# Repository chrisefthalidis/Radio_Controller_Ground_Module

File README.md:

This board is an embedded system, based on the STM32F411CCU6 microcontroller. It incorporates an nRF24L01+ radio
transceiver with an analog front-end (RFX2401C) for signal amplification. Inside the 'Hardware' folder, you will
find all the necessary PCB design files from KiCad. Inside the 'Firmware' folder, you will find all the relevant
HAL drivers generated by STM32CubeMX, as well as an nRF24L01+ SPI driver. This board is complementary to the Flight
Controller board that you will find on my GitHub page. The basic idea is that we read the value of the on-board 
potentiometer through an ADC via DMA and we transmit this value via radio to the Flight Controller, which in turn
controls the speed of the quadcopter's motors.

P.S. This board is not perfect in any way. It has some design mistakes, because it's one of my earlier boards, but
it WORKS fine. With each board that i design, i learn new stuff and keep getting better. If you have any questions
on how to use this board, please contact me at chrisefthalidis@gmail.com

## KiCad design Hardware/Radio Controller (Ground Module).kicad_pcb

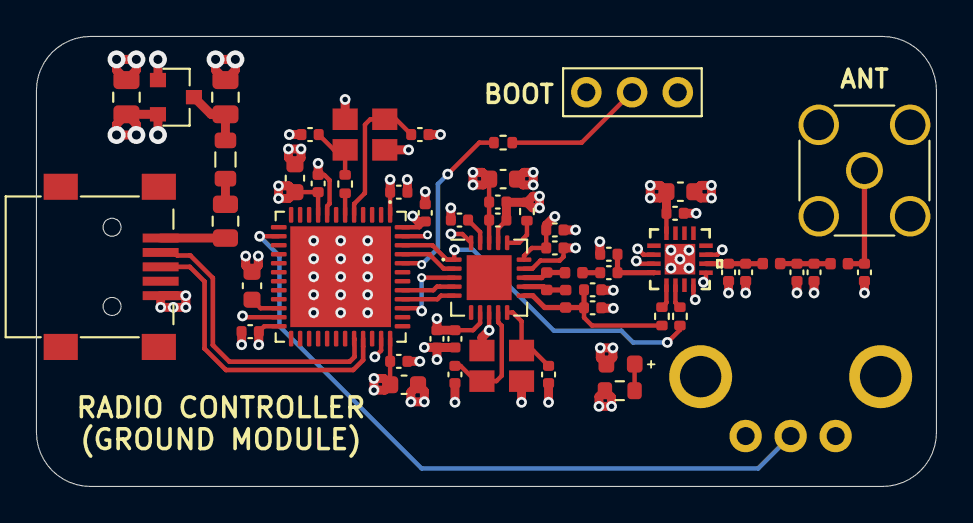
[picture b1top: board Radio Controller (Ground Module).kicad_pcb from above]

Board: 4 copper layers, 50.0 x 25.0 mm, 57 parts (0 on the bottom side), 34 nets.

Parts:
C1, C2: 10uF; C_0805_2012Metric
C3, C24, C31: 4.7uF; C_0603_1608Metric
C4, C6, C8: 10nF; C_0402_1005Metric
C5, C7, C9: 1nF; C_0402_1005Metric
C10, C29: 1uF; C_0603_1608Metric
C11: 220pF; C_0402_1005Metric
C12: 4.7pF; C_0402_1005Metric
C13: 2.2nF; C_0402_1005Metric
C14, C20, C21, C22, C23: 1.5pF; C_0402_1005Metric
C15: 1pF; C_0402_1005Metric
C16: 33nF; C_0402_1005Metric
C17, C18, C32, C33: 12pF; C_0402_1005Metric
C19: 0.3pF; C_0402_1005Metric
C25, C26, C27, C28, C30: 100nF; C_0402_1005Metric
D1: Green LED; LED_0603_1608Metric
F1: Fuse; Fuse_0805_2012Metric
FB1: GZ2012D601TF; L_0805_2012Metric
J1: USB_B_Mini; USB_Mini-B_Lumberg_2486_01_Horizontal
J2: KH-SMA-KE8-G; SMA_Amphenol_132291_Vertical
J3: Conn_01x03; PinHeader_1x03_P2.54mm_Vertical
L1: 2.7nH; L_0402_1005Metric
L2: 8.2nH; L_0402_1005Metric
L3: 3.9nH; L_0402_1005Metric
L4, L5: 2.4nH; L_0402_1005Metric
R1: 330Ω; R_0603_1608Metric
R2, R3: 1ΚΩ; R_0402_1005Metric
R4: 22ΚΩ; R_0402_1005Metric
R5: 10ΚΩ; R_0402_1005Metric
R6: 47Ω; R_0402_1005Metric
RV1: R_POT; Potentiometer_Alps_RK09K_Single_Horizontal
U1: XC6206P332MR; SOT-23
U2: RFX2401C
U3: nRF24L01P; QFN-20-1EP_4x4mm_P0.5mm_EP2.5x2.5mm
U4: STM32F411CCUx; QFN-48-1EP_7x7mm_P0.5mm_EP5.6x5.6mm
Y1, Y2: X322516MLB4SI; Crystal_SMD_3225-4Pin_3.2x2.5mm

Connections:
+3V3: C2.1, C3.1, C4.1, C5.1, C6.1, C7.1, C8.1, C9.1, C10.1, C11.1, C24.1, C25.1, C26.1, C27.1, C28.1, C29.1, C30.1, J3.1, R1.1, RV1.1, U1.2, U2.16, U3.7, U3.15, U3.18, U4.1, U4.9, U4.24, U4.36, U4.48
/ADC_IN: RV1.2, U4.14
/ANT: C19.1, C20.1, L4.2, U2.10
/ANT1: L1.2, L2.1, U3.12
/ANT2: L2.2, L3.2, U3.13
/BOOT0: R5.1, U4.44
/CE: R3.1, U3.1, U4.46
/CSN: U3.2, U4.45
/LDO_VIN: C1.1, FB1.1, U1.3
/LED_RES: D1.2, R1.2
/MISO: U3.5, U4.40
/MOSI: U3.4, U4.41
/OSC_IN: C32.1, U4.5, Y2.1
/OSC_OUT: R6.2, U4.6
/RXEN: R3.2, U2.6
/SCK: U3.3, U4.39
/TXEN: R2.2, U2.5
/TXRX: C14.1, C15.1, U2.4
/USB_D+: J1.3, U4.33
/USB_D-: J1.2, U4.32
/VCAP1: C31.2, U4.22
/VDD_PA: C12.1, C13.1, L1.1, R2.1, U3.11
/XC1: C17.1, U3.10, Y1.1
/XC2: C18.1, U3.9, Y1.3
GND: C1.2, C2.2, C3.2, C4.2, C5.2, C6.2, C7.2, C8.2, C9.2, C10.2, C11.2, C12.2, C13.2, C15.2, C16.2, C17.2, C18.2, C19.2, C20.2, C21.2, C22.2, C23.2, C24.2, C25.2, C26.2, C27.2, C28.2, C29.2, C30.2, C31.1, C32.2, C33.2, D1.1, J1.5, J2.2, J3.3, R4.1, RV1.3, U1.1, U2.2, U2.3, U2.8, U2.9, U2.11, U2.17, U3.8, U3.14, U3.17, U3.20, U4.8, U4.23, U4.35, U4.47, U4.49, Y1.2, Y1.4, Y2.2, Y2.4
unnamed: C14.2, L3.1
unnamed: C16.1, U3.19
unnamed: C21.1, C22.1, L4.1, L5.2
unnamed: C23.1, J2.1, L5.1
unnamed: C33.1, R6.1, Y2.3
unnamed: F1.1, FB1.2
unnamed: J3.2, R5.2
unnamed: R4.2, U3.16
VBUS: F1.2, J1.1

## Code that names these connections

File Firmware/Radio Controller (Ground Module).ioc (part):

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Mcu.Name=STM32F411C(C-E)Ux
Mcu.Package=UFQFPN48
Mcu.UserName=STM32F411CCUx
PA11.Mode=Device_Only
PA11.Signal=USB_OTG_FS_DM
PA12.Mode=Device_Only
PA12.Signal=USB_OTG_FS_DP
PA4.Signal=ADCx_IN4
PB3.Mode=Full_Duplex_Master
PB3.Signal=SPI3_SCK
PB4.Mode=Full_Duplex_Master
PB4.Signal=SPI3_MISO
PB5.Mode=Full_Duplex_Master
PB5.Signal=SPI3_MOSI
PB8.GPIOParameters=GPIO_Label
PB8.GPIO_Label=CSN
PB8.Signal=GPIO_Output
PB9.GPIOParameters=GPIO_Label
PB9.GPIO_Label=CE
PB9.Signal=GPIO_Output
PH0\ -\ OSC_IN.Mode=HSE-External-Oscillator
PH0\ -\ OSC_IN.Signal=RCC_OSC_IN
PH1\ -\ OSC_OUT.Mode=HSE-External-Oscillator
PH1\ -\ OSC_OUT.Signal=RCC_OSC_OUT
RCC.HSE_VALUE=16000000
RCC.SYSCLKFreq_VALUE=96000000.00000001
RCC.SYSCLKSource=RCC_SYSCLKSOURCE_PLLCLK
board=custom

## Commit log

2021-10-31 Add more comments
2021-11-27 Update Build directory
2021-11-27 Add DMA driver
2021-11-27 Modify JSON files
2021-11-27 Add DMA in STM32CubeMX
2021-11-27 Update STM32CubeMX file
2021-11-27 Update Makefile
2021-11-27 Modify file
2021-11-27 Add DMA functionality
